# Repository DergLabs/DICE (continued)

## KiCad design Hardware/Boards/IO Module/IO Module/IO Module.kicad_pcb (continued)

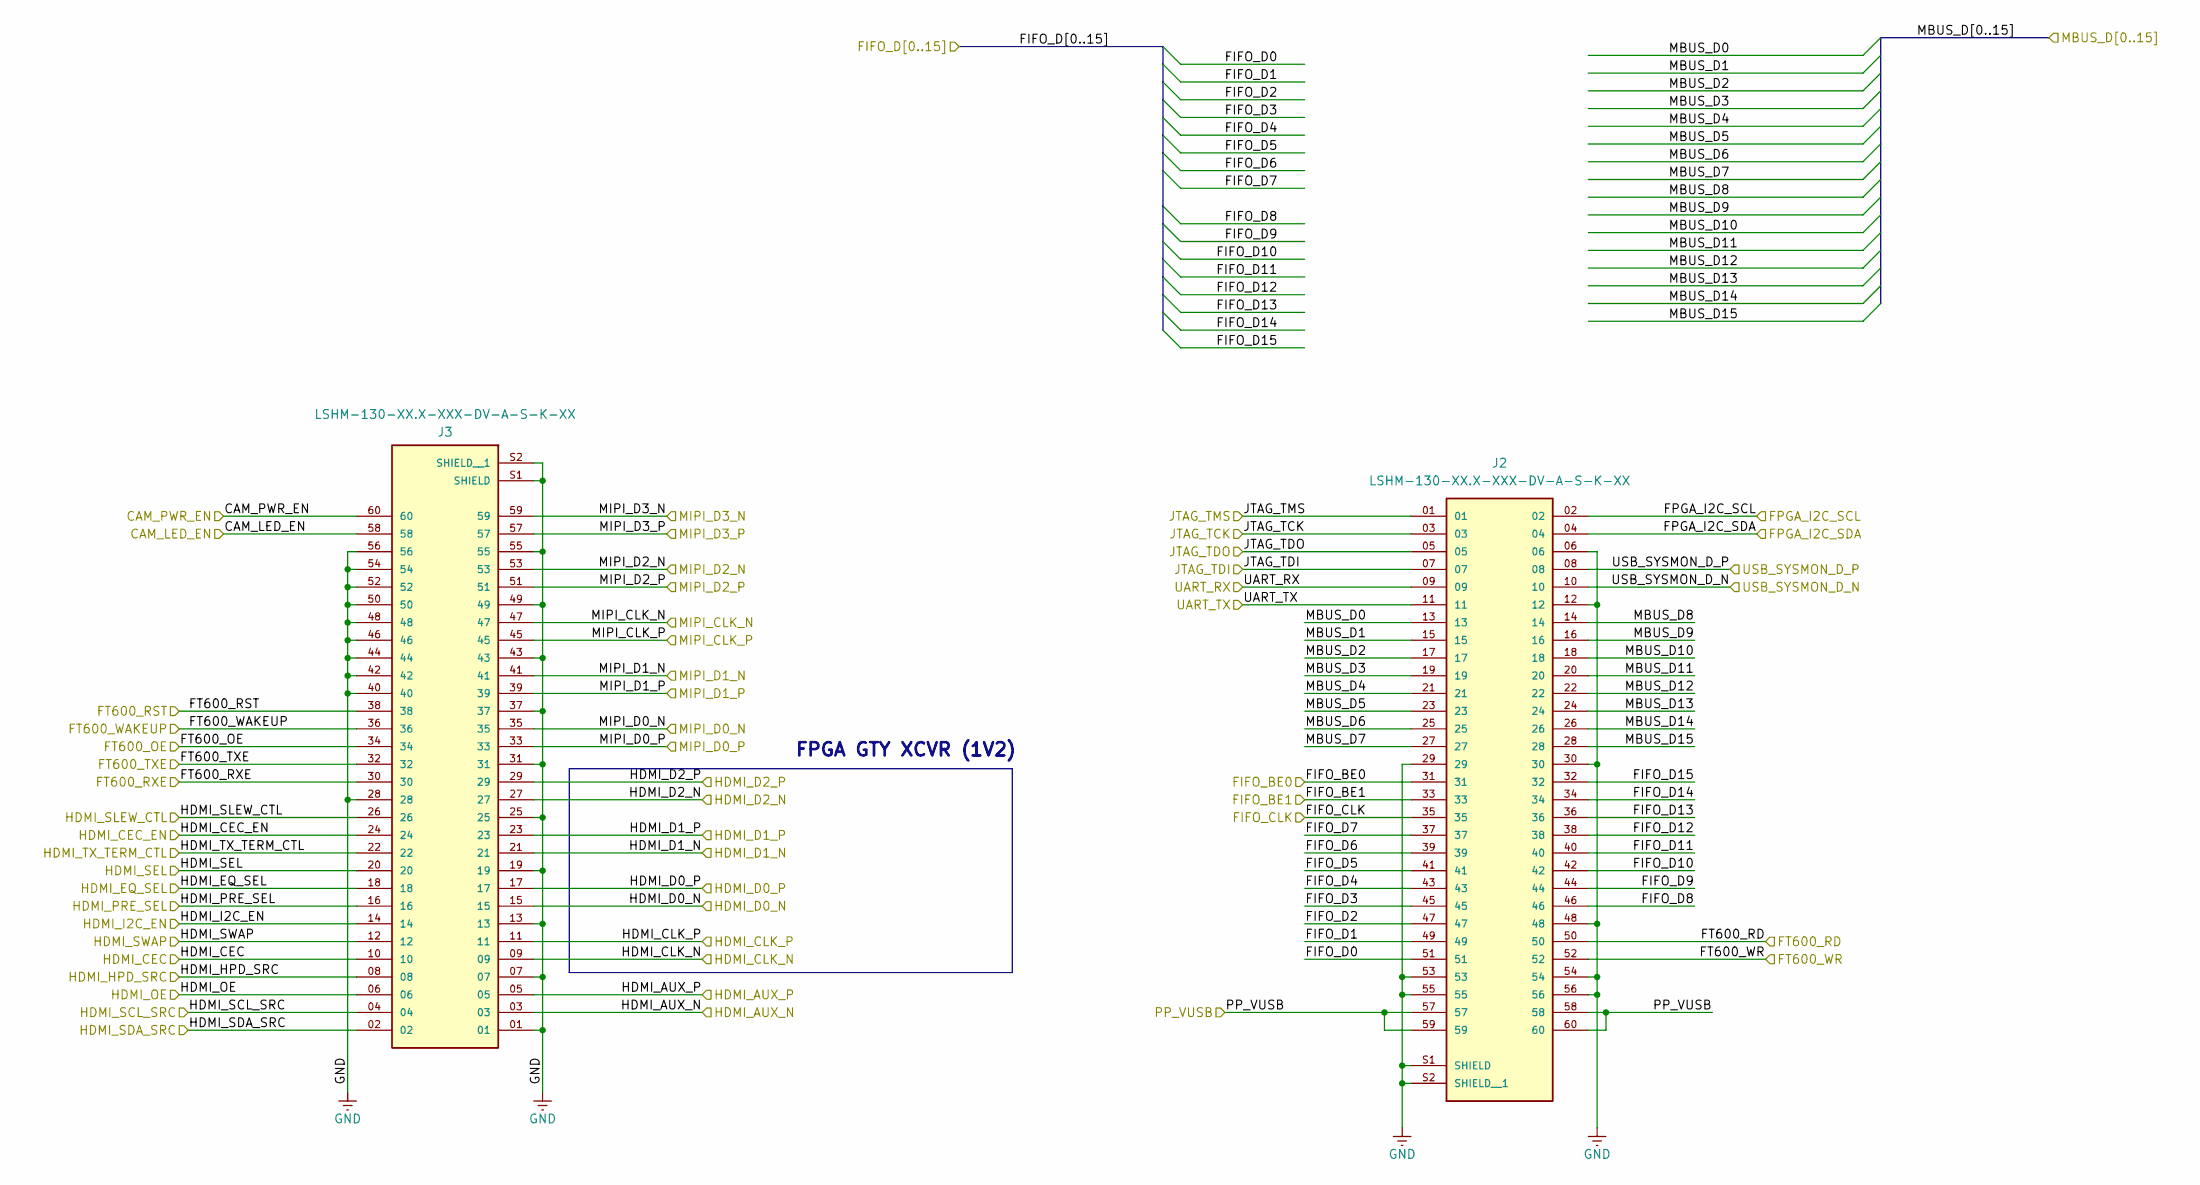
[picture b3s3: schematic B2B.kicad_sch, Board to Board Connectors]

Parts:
J2, J3: LSHM-130-XX.X-XXX-DV-A-S-K-XX; SAMTEC_LSHM-130-XX.X-XXX-DV-A-S-K-XX; PARTREV G

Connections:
/Top/B2B/CAM_LED_EN: J3.58; also elsewhere on the board
/Top/B2B/CAM_PWR_EN: J3.60; also elsewhere on the board
/Top/B2B/FIFO_BE0: J2.31; also elsewhere on the board
/Top/B2B/FIFO_BE1: J2.33; also elsewhere on the board
/Top/B2B/FIFO_CLK: J2.35; also elsewhere on the board
/Top/B2B/FIFO_D0: J2.51; also elsewhere on the board
/Top/B2B/FIFO_D1: J2.49; also elsewhere on the board
/Top/B2B/FIFO_D2: J2.47; also elsewhere on the board
/Top/B2B/FIFO_D3: J2.45; also elsewhere on the board
/Top/B2B/FIFO_D4: J2.43; also elsewhere on the board
/Top/B2B/FIFO_D5: J2.41; also elsewhere on the board
/Top/B2B/FIFO_D6: J2.39; also elsewhere on the board
/Top/B2B/FIFO_D7: J2.37; also elsewhere on the board
/Top/B2B/FIFO_D8: J2.46; also elsewhere on the board
/Top/B2B/FIFO_D9: J2.44; also elsewhere on the board
/Top/B2B/FIFO_D10: J2.42; also elsewhere on the board
/Top/B2B/FIFO_D11: J2.40; also elsewhere on the board
/Top/B2B/FIFO_D12: J2.38; also elsewhere on the board
/Top/B2B/FIFO_D13: J2.36; also elsewhere on the board
/Top/B2B/FIFO_D14: J2.34; also elsewhere on the board
/Top/B2B/FIFO_D15: J2.32; also elsewhere on the board
/Top/B2B/FPGA_I2C_SCL: J2.02; also elsewhere on the board
/Top/B2B/FPGA_I2C_SDA: J2.04; also elsewhere on the board
/Top/B2B/FT600_OE: J3.34; also elsewhere on the board
/Top/B2B/FT600_RD: J2.50; also elsewhere on the board
/Top/B2B/FT600_RST: J3.38; also elsewhere on the board
/Top/B2B/FT600_RXE: J3.30; also elsewhere on the board
/Top/B2B/FT600_TXE: J3.32; also elsewhere on the board
/Top/B2B/FT600_WAKEUP: J3.36; also elsewhere on the board
/Top/B2B/FT600_WR: J2.52; also elsewhere on the board
/Top/B2B/HDMI_AUX_N: J3.03; also elsewhere on the board
/Top/B2B/HDMI_AUX_P: J3.05; also elsewhere on the board
/Top/B2B/HDMI_CEC: J3.10; also elsewhere on the board
/Top/B2B/HDMI_CEC_EN: J3.24; also elsewhere on the board
/Top/B2B/HDMI_CLK_N: J3.09; also elsewhere on the board
/Top/B2B/HDMI_CLK_P: J3.11; also elsewhere on the board
/Top/B2B/HDMI_D0_N: J3.15; also elsewhere on the board
/Top/B2B/HDMI_D0_P: J3.17; also elsewhere on the board
/Top/B2B/HDMI_D1_N: J3.21; also elsewhere on the board
/Top/B2B/HDMI_D1_P: J3.23; also elsewhere on the board
/Top/B2B/HDMI_D2_N: J3.27; also elsewhere on the board
/Top/B2B/HDMI_D2_P: J3.29; also elsewhere on the board
/Top/B2B/HDMI_EQ_SEL: J3.18; also elsewhere on the board
/Top/B2B/HDMI_HPD_SRC: J3.08; also elsewhere on the board
/Top/B2B/HDMI_I2C_EN: J3.14; also elsewhere on the board
/Top/B2B/HDMI_OE: J3.06; also elsewhere on the board
/Top/B2B/HDMI_PRE_SEL: J3.16; also elsewhere on the board
/Top/B2B/HDMI_SCL_SRC: J3.04; also elsewhere on the board
/Top/B2B/HDMI_SDA_SRC: J3.02; also elsewhere on the board
/Top/B2B/HDMI_SEL: J3.20; also elsewhere on the board
/Top/B2B/HDMI_SLEW_CTL: J3.26; also elsewhere on the board
/Top/B2B/HDMI_SWAP: J3.12; also elsewhere on the board
/Top/B2B/HDMI_TX_TERM_CTL: J3.22; also elsewhere on the board
/Top/B2B/JTAG_TCK: J2.03; also elsewhere on the board
/Top/B2B/JTAG_TDI: J2.07; also elsewhere on the board
/Top/B2B/JTAG_TDO: J2.05; also elsewhere on the board
/Top/B2B/JTAG_TMS: J2.01; also elsewhere on the board
/Top/B2B/MBUS_D0: J2.13; also elsewhere on the board
/Top/B2B/MBUS_D1: J2.15; also elsewhere on the board
/Top/B2B/MBUS_D2: J2.17; also elsewhere on the board
/Top/B2B/MBUS_D3: J2.19; also elsewhere on the board
/Top/B2B/MBUS_D4: J2.21; also elsewhere on the board
/Top/B2B/MBUS_D5: J2.23; also elsewhere on the board
/Top/B2B/MBUS_D6: J2.25; also elsewhere on the board
/Top/B2B/MBUS_D7: J2.27; also elsewhere on the board
/Top/B2B/MBUS_D8: J2.14; also elsewhere on the board
/Top/B2B/MBUS_D9: J2.16; also elsewhere on the board
/Top/B2B/MBUS_D10: J2.18; also elsewhere on the board
/Top/B2B/MBUS_D11: J2.20; also elsewhere on the board
/Top/B2B/MBUS_D12: J2.22; also elsewhere on the board
/Top/B2B/MBUS_D13: J2.24; also elsewhere on the board
/Top/B2B/MBUS_D14: J2.26; also elsewhere on the board
/Top/B2B/MBUS_D15: J2.28; also elsewhere on the board
/Top/B2B/MIPI_CLK_N: J3.47; also elsewhere on the board
/Top/B2B/MIPI_CLK_P: J3.45; also elsewhere on the board
/Top/B2B/MIPI_D0_N: J3.35; also elsewhere on the board
/Top/B2B/MIPI_D0_P: J3.33; also elsewhere on the board
/Top/B2B/MIPI_D1_N: J3.41; also elsewhere on the board
/Top/B2B/MIPI_D1_P: J3.39; also elsewhere on the board
/Top/B2B/MIPI_D2_N: J3.53; also elsewhere on the board
/Top/B2B/MIPI_D2_P: J3.51; also elsewhere on the board
/Top/B2B/MIPI_D3_N: J3.59; also elsewhere on the board
/Top/B2B/MIPI_D3_P: J3.57; also elsewhere on the board
/Top/B2B/UART_RX: J2.09; also elsewhere on the board
/Top/B2B/UART_TX: J2.11; also elsewhere on the board
/Top/B2B/USB_SYSMON_D_N: J2.10; also elsewhere on the board
/Top/B2B/USB_SYSMON_D_P: J2.08; also elsewhere on the board
/Top/PP_VUSB: J2.57, J2.58, J2.59, J2.60; also elsewhere on the board
GND: J2.06, J2.12, J2.29, J2.30, J2.48, J2.53, J2.54, J2.55, J2.56, J2.S1 (SHIELD), J2.S2 (SHIELD__1), J3.01, J3.07, J3.13, J3.19, J3.25, J3.28, J3.31, J3.37, J3.40, J3.42, J3.43, J3.44, J3.46, J3.48, J3.49, J3.50, J3.52, J3.54, J3.55, J3.56, J3.S1 (SHIELD), J3.S2 (SHIELD__1); also elsewhere on the board

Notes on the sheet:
FPGA GTY XCVR (1V2)

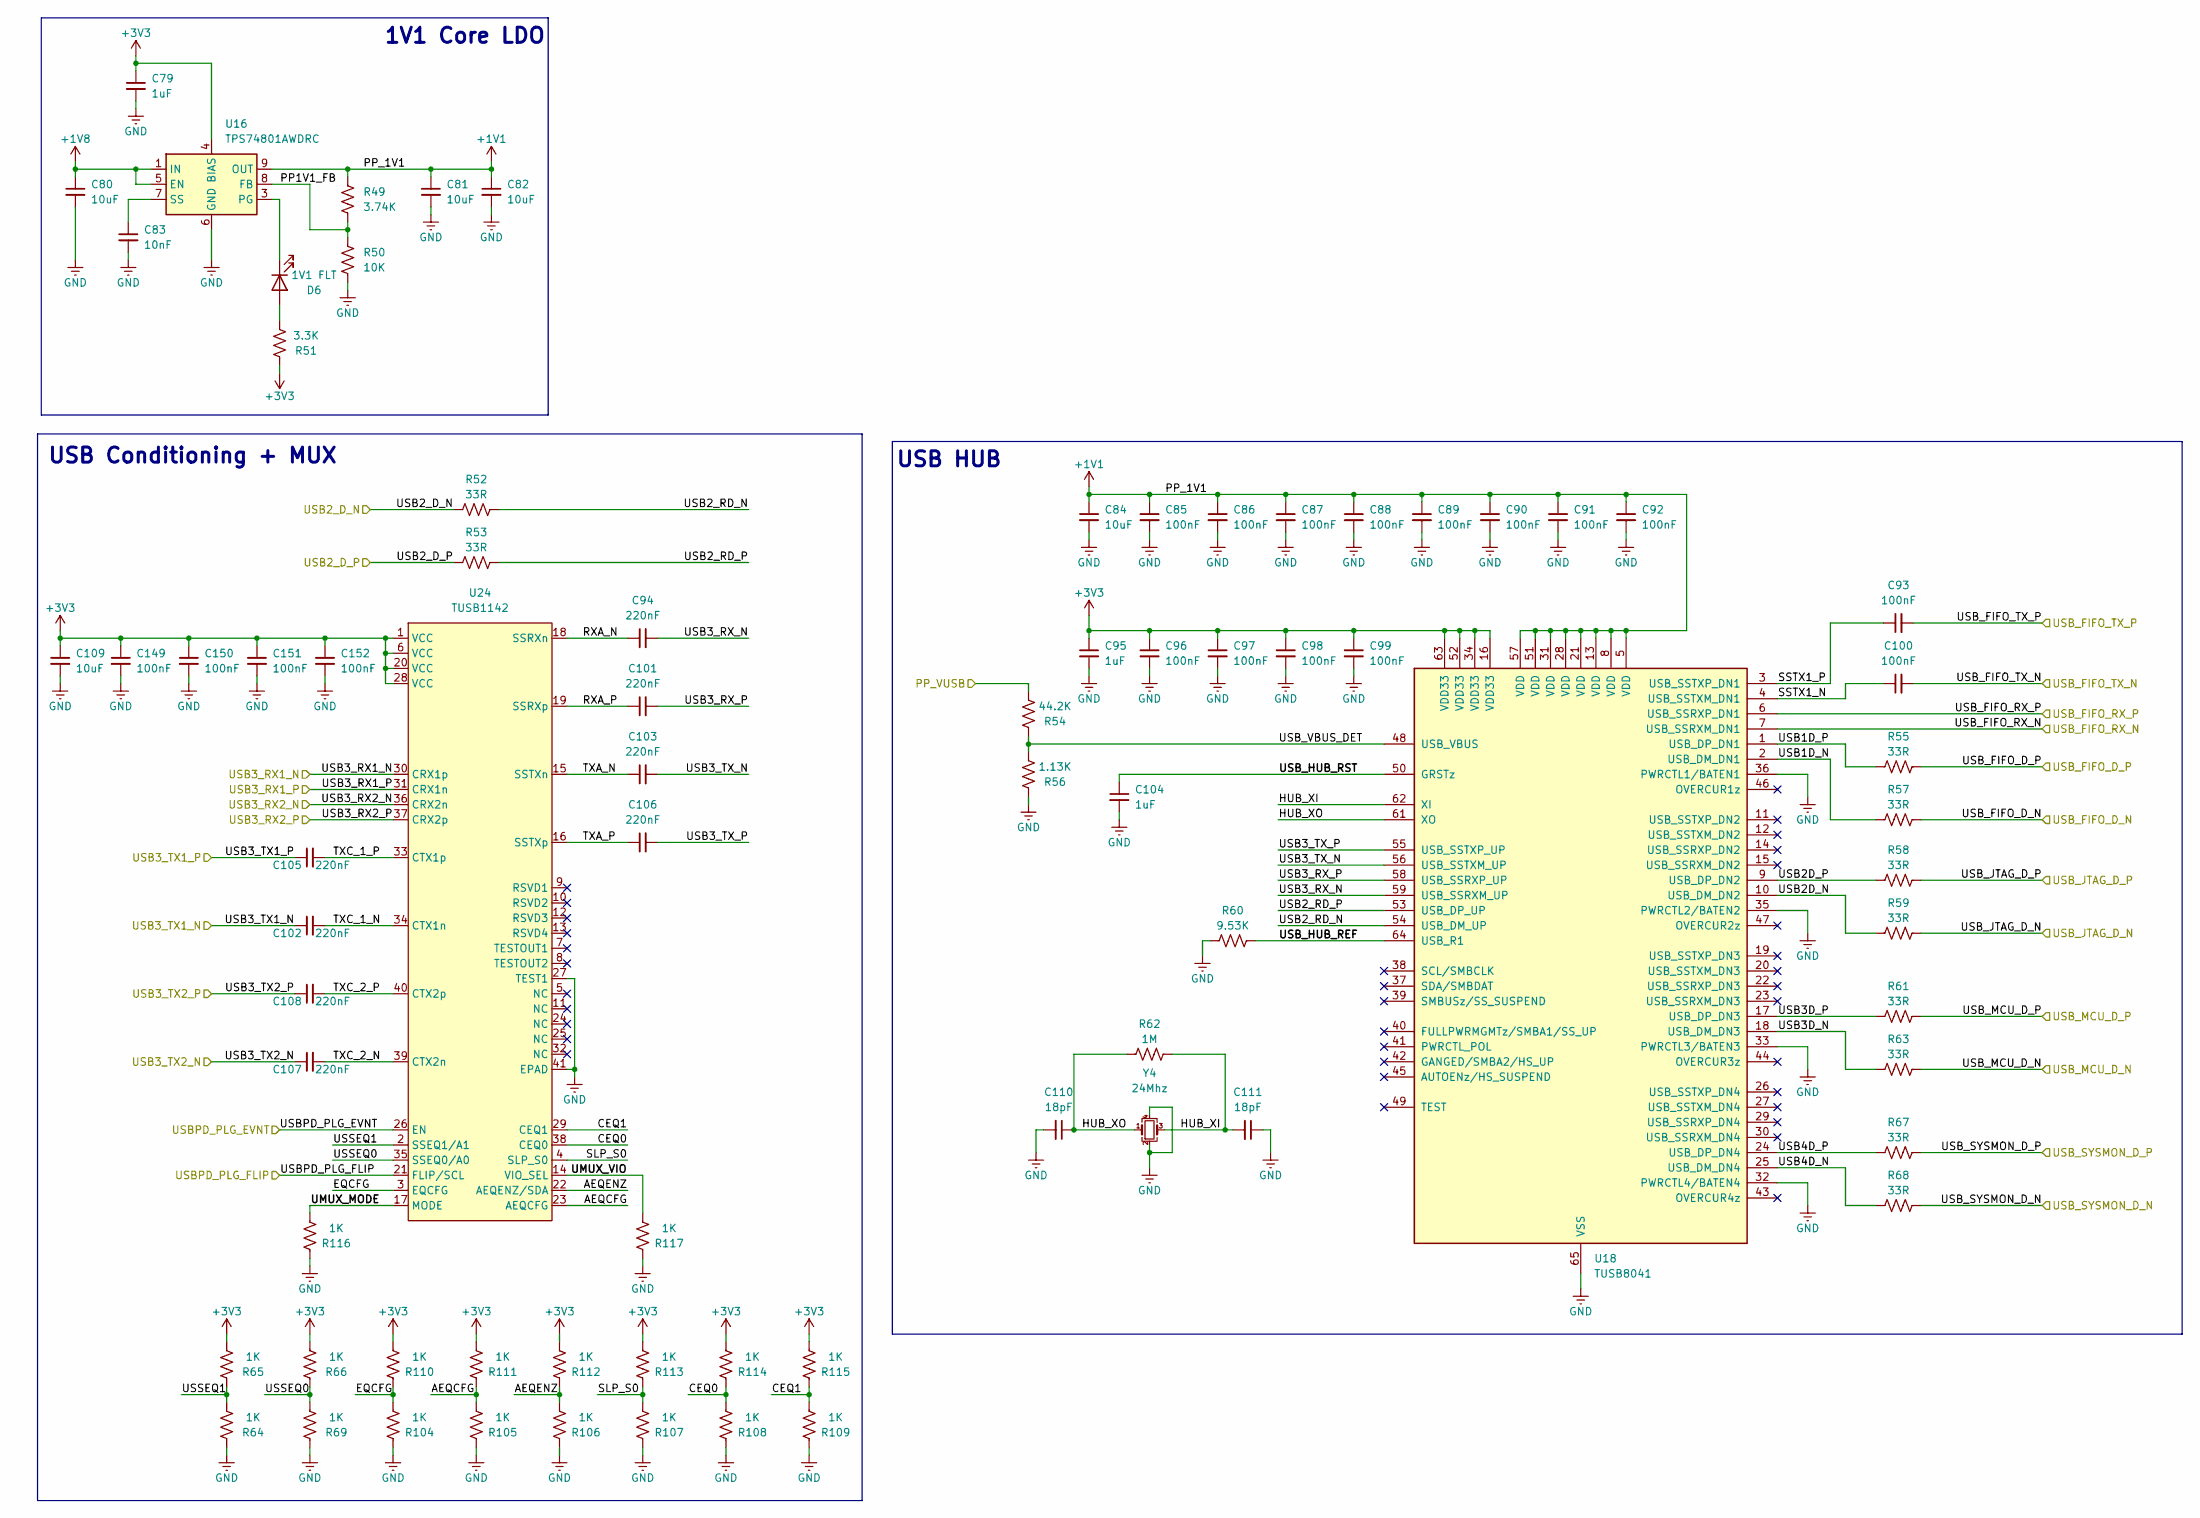
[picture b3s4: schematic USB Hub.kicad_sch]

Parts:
C79, C95, C104: 1uF; C_0201_0603Metric
C80, C81, C82, C84, C109: 10uF; C_0603_1608Metric
C83: 10nF; C_0201_0603Metric
C85, C86, C87, C88, C89, C90, C91, C92, C93, C96, C97, C98, C99, C100, C149, C150, C151, C152: 100nF; C_0201_0603Metric
C94, C101, C102, C103, C105, C106, C107, C108: 220nF; C_0201_0603Metric
C110, C111: 18pF; C_0201_0603Metric
D6: 1V1 FLT; LED_0603_1608Metric
R49: 3.74K; R_0201_0603Metric
R50: 10K; R_0201_0603Metric
R51: 3.3K; R_0201_0603Metric
R52, R53, R55, R57, R58, R59, R61, R63, R67, R68: 33R; R_0201_0603Metric
R54: 44.2K; R_0201_0603Metric
R56: 1.13K; R_0201_0603Metric
R60: 9.53K; R_0201_0603Metric
R62: 1M; R_0201_0603Metric
R64, R65, R66, R69, R104, R105, R106, R107, R108, R109, R110, R111, R112, R113, R114, R115, R116, R117: 1K; R_0201_0603Metric
U16: TPS74801AWDRC; VSON-10-1EP_3x3mm_P0.5mm_EP1.65x2.4mm_ThermalVias
U18: TUSB8041; QFN-64-1EP_9x9mm_P0.5mm_EP6x6mm_ThermalVias
U24: TUSB1142; WQFN_142RNQT_TEX
Y4: 24Mhz; Oscillator_SMD_Abracon_ASE-4Pin_3.2x2.5mm

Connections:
+1V1: C81.1, C82.1, C84.1, C85.1, C86.1, C87.1, C88.1, C89.1, C90.1, C91.1, C92.1, R49.2, U16.9 (OUT), U16.10 (OUT), U18.5 (VDD), U18.8 (VDD), U18.13 (VDD), U18.21 (VDD), U18.28 (VDD), U18.31 (VDD), U18.51 (VDD), U18.57 (VDD)
+1V8: C80.1, U16.1 (IN), U16.2 (IN), U16.5 (EN); also elsewhere on the board
+3V3: C79.1, C95.1, C96.1, C97.1, C98.1, C99.1, C109.1, C149.1, C150.1, C151.1, C152.1, R51.1, R65.2, R66.2, R110.2, R111.2, R112.2, R113.2, R114.2, R115.2, U16.4 (BIAS), U18.16 (VDD33), U18.34 (VDD33), U18.52 (VDD33), U18.63 (VDD33), U24.1 (VCC), U24.6 (VCC), U24.20 (VCC), U24.28 (VCC); also elsewhere on the board
/Top/B2B/USB_SYSMON_D_N: R68.1; also elsewhere on the board
/Top/B2B/USB_SYSMON_D_P: R67.1; also elsewhere on the board
/Top/MCU/USBPD_PLG_EVNT: U24.26 (EN); also elsewhere on the board
/Top/MCU/USBPD_PLG_FLIP: U24.21 (FLIP/SCL); also elsewhere on the board
/Top/MCU/USB_MCU_D_N: R63.1; also elsewhere on the board
/Top/MCU/USB_MCU_D_P: R61.1; also elsewhere on the board
/Top/PP_VUSB: R54.2; also elsewhere on the board
/Top/Power/USB2_D_N: R52.2; also elsewhere on the board
/Top/Power/USB2_D_P: R53.2; also elsewhere on the board
/Top/Power/USB3_RX1_N: U24.30 (CRX1p); also elsewhere on the board
/Top/Power/USB3_RX1_P: U24.31 (CRX1n); also elsewhere on the board
/Top/Power/USB3_RX2_N: U24.36 (CRX2n); also elsewhere on the board
/Top/Power/USB3_RX2_P: U24.37 (CRX2p); also elsewhere on the board
/Top/Power/USB3_TX1_N: C102.1; also elsewhere on the board
/Top/Power/USB3_TX1_P: C105.1; also elsewhere on the board
/Top/Power/USB3_TX2_N: C107.1; also elsewhere on the board
/Top/Power/USB3_TX2_P: C108.1; also elsewhere on the board
/Top/USB Hub/AEQCFG: R105.2, R111.1, U24.23 (AEQCFG)
/Top/USB Hub/AEQENZ: R106.2, R112.1, U24.22 (AEQENZ/SDA)
/Top/USB Hub/CEQ0: R108.2, R114.1, U24.38 (CEQ0)
/Top/USB Hub/CEQ1: R109.2, R115.1, U24.29 (CEQ1)
/Top/USB Hub/EQCFG: R104.2, R110.1, U24.3 (EQCFG)
/Top/USB Hub/HUB_XI: C111.2, R62.1, U18.62 (XI), Y4.3
/Top/USB Hub/HUB_XO: C110.1, R62.2, U18.61 (XO), Y4.1
/Top/USB Hub/PP1V1_FB: R49.1, R50.2, U16.8 (FB)
/Top/USB Hub/RXA_N: C94.1, U24.18 (SSRXn)
/Top/USB Hub/RXA_P: C101.1, U24.19 (SSRXp)
/Top/USB Hub/SLP_S0: R107.2, R113.1, U24.4 (SLP_S0)
/Top/USB Hub/SSTX1_N: C100.1, U18.4 (USB_SSTXM_DN1)
/Top/USB Hub/SSTX1_P: C93.1, U18.3 (USB_SSTXP_DN1)
/Top/USB Hub/TXA_N: C103.1, U24.15 (SSTXn)
/Top/USB Hub/TXA_P: C106.1, U24.16 (SSTXp)
/Top/USB Hub/TXC_1_N: C102.2, U24.34 (CTX1n)
/Top/USB Hub/TXC_1_P: C105.2, U24.33 (CTX1p)
/Top/USB Hub/TXC_2_N: C107.2, U24.39 (CTX2n)
/Top/USB Hub/TXC_2_P: C108.2, U24.40 (CTX2p)
/Top/USB Hub/UMUX_MODE: R116.2, U24.17 (MODE)
/Top/USB Hub/UMUX_VIO: R117.2, U24.14 (VIO_SEL)
/Top/USB Hub/USB1D_N: R57.2, U18.2 (USB_DM_DN1)
/Top/USB Hub/USB1D_P: R55.2, U18.1 (USB_DP_DN1)
/Top/USB Hub/USB2D_N: R59.2, U18.10 (USB_DM_DN2)
/Top/USB Hub/USB2D_P: R58.2, U18.9 (USB_DP_DN2)
/Top/USB Hub/USB2_RD_N: R52.1, U18.54 (USB_DM_UP)
/Top/USB Hub/USB2_RD_P: R53.1, U18.53 (USB_DP_UP)
/Top/USB Hub/USB3D_N: R63.2, U18.18 (USB_DM_DN3)
/Top/USB Hub/USB3D_P: R61.2, U18.17 (USB_DP_DN3)
/Top/USB Hub/USB3_RX_N: C94.2, U18.59 (USB_SSRXM_UP)
/Top/USB Hub/USB3_RX_P: C101.2, U18.58 (USB_SSRXP_UP)
/Top/USB Hub/USB3_TX_N: C103.2, U18.56 (USB_SSTXM_UP)
/Top/USB Hub/USB3_TX_P: C106.2, U18.55 (USB_SSTXP_UP)
/Top/USB Hub/USB4D_N: R68.2, U18.25 (USB_DM_DN4)
/Top/USB Hub/USB4D_P: R67.2, U18.24 (USB_DP_DN4)
/Top/USB Hub/USB_FIFO_D_N: R57.1; also elsewhere on the board
/Top/USB Hub/USB_FIFO_D_P: R55.1; also elsewhere on the board
/Top/USB Hub/USB_FIFO_RX_N: U18.7 (USB_SSRXM_DN1); also elsewhere on the board
/Top/USB Hub/USB_FIFO_RX_P: U18.6 (USB_SSRXP_DN1); also elsewhere on the board
/Top/USB Hub/USB_FIFO_TX_N: C100.2; also elsewhere on the board
/Top/USB Hub/USB_FIFO_TX_P: C93.2; also elsewhere on the board
/Top/USB Hub/USB_HUB_REF: R60.1, U18.64 (USB_R1)
/Top/USB Hub/USB_HUB_RST: C104.1, U18.50 (GRSTz)
/Top/USB Hub/USB_JTAG_D_N: R59.1; also elsewhere on the board
/Top/USB Hub/USB_JTAG_D_P: R58.1; also elsewhere on the board
/Top/USB Hub/USB_VBUS_DET: R54.1, R56.2, U18.48 (USB_VBUS)
/Top/USB Hub/USSEQ0: R66.1, R69.2, U24.35 (SSEQ0/A0)
/Top/USB Hub/USSEQ1: R64.2, R65.1, U24.2 (SSEQ1/A1)
GND: C79.2, C80.2, C81.2, C82.2, C83.2, C84.2, C85.2, C86.2, C87.2, C88.2, C89.2, C90.2, C91.2, C92.2, C95.2, C96.2, C97.2, C98.2, C99.2, C104.2, C109.2, C110.2, C111.1, C149.2, C150.2, C151.2, C152.2, R50.1, R56.1, R60.2, R64.1, R69.1, R104.1, R105.1, R106.1, R107.1, R108.1, R109.1, R116.1, R117.1, U16.6 (GND), U16.11 (GND), U18.32 (PWRCTL4/BATEN4), U18.33 (PWRCTL3/BATEN3), U18.35 (PWRCTL2/BATEN2), U18.36 (PWRCTL1/BATEN1), U18.65 (VSS), U24.27 (TEST1), U24.41 (EPAD), Y4.2, Y4.4; also elsewhere on the board
unnamed: D6.2 (A), R51.2
unnamed: D6.1 (K), U16.3 (PG)
unnamed: C83.1, U16.7 (SS)

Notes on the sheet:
USB Conditioning + MUX
1V1 Core LDO
USB HUB

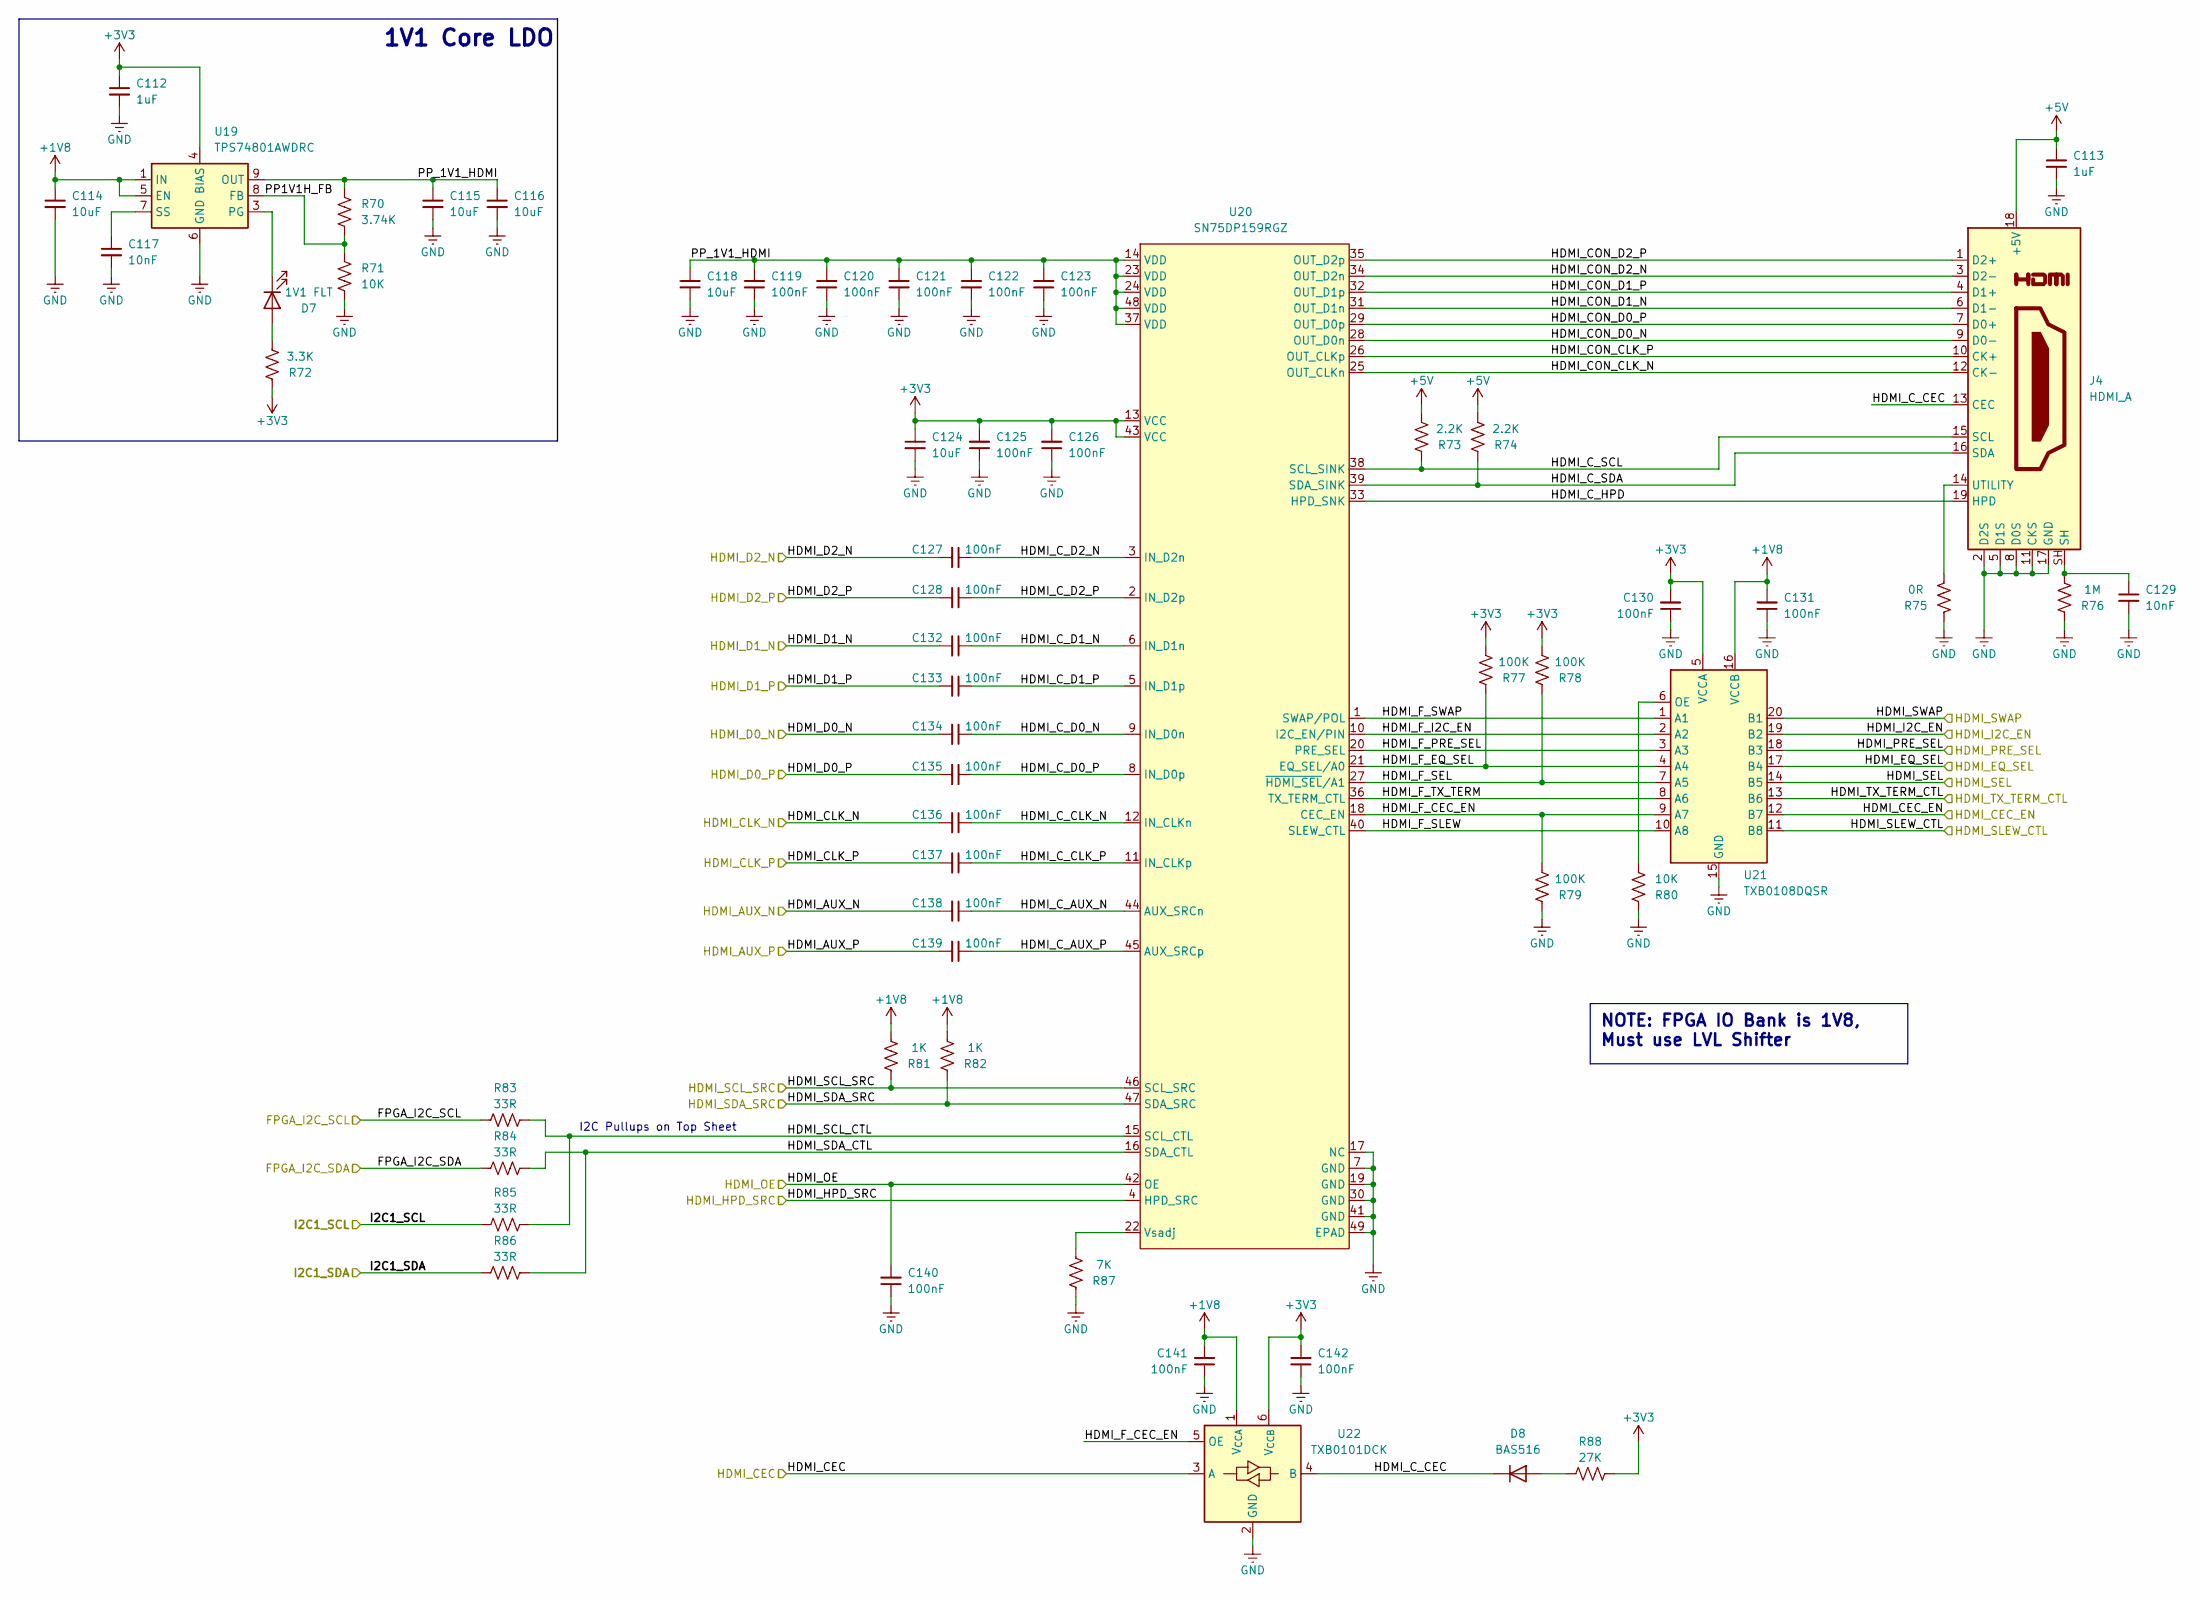
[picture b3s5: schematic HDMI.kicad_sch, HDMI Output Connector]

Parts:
C112, C113: 1uF; C_0201_0603Metric
C114, C115, C116, C118, C124: 10uF; C_0603_1608Metric
C117, C129: 10nF; C_0201_0603Metric
C119, C120, C121, C122, C123, C125, C126, C127, C128, C130, C131, C132, C133, C134, C135, C136, C137, C138, C139, C140, C141, C142: 100nF; C_0201_0603Metric
D7: 1V1 FLT; LED_0603_1608Metric
D8: BAS516; D_SOD-523
J4: HDMI_A; HDMI_A_Molex_208658-1001_Horizontal
R70: 3.74K; R_0201_0603Metric
R71, R80: 10K; R_0201_0603Metric
R72: 3.3K; R_0201_0603Metric
R73, R74: 2.2K; R_0201_0603Metric
R75: 0R; R_0201_0603Metric
R76: 1M; R_0201_0603Metric
R77, R78, R79: 100K; R_0201_0603Metric
R81, R82: 1K; R_0201_0603Metric
R83, R84, R85, R86: 33R; R_0201_0603Metric
R87: 7K; R_0201_0603Metric
R88: 27K; R_0201_0603Metric
U19: TPS74801AWDRC; VSON-10-1EP_3x3mm_P0.5mm_EP1.65x2.4mm_ThermalVias
U20: SN75DP159RGZ; QFN-48-1EP_7x7mm_P0.5mm_EP5.1x5.1mm
U21: TXB0108DQSR; USON-20_2x4mm_P0.4mm
U22: TXB0101DCK; SOT-363_SC-70-6

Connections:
+1V8: C114.1, C131.2, C141.2, R81.2, R82.2, U19.1 (IN), U19.2 (IN), U19.5 (EN), U21.16 (VCCB), U22.1 (V_{CCA}); also elsewhere on the board
+3V3: C112.1, C124.1, C125.2, C126.2, C130.2, C142.2, R72.1, R77.2, R78.2, R88.1, U19.4 (BIAS), U20.13 (VCC), U20.43 (VCC), U21.5 (VCCA), U22.6 (V_{CCB}); also elsewhere on the board
+5V: C113.1, J4.18 (+5V), R73.2, R74.2
/Top/B2B/FPGA_I2C_SCL: R83.2; also elsewhere on the board
/Top/B2B/FPGA_I2C_SDA: R84.2; also elsewhere on the board
/Top/B2B/HDMI_AUX_N: C138.2; also elsewhere on the board
/Top/B2B/HDMI_AUX_P: C139.2; also elsewhere on the board
/Top/B2B/HDMI_CEC: U22.3 (A); also elsewhere on the board
/Top/B2B/HDMI_CEC_EN: U21.12 (B7); also elsewhere on the board
/Top/B2B/HDMI_CLK_N: C136.2; also elsewhere on the board
/Top/B2B/HDMI_CLK_P: C137.2; also elsewhere on the board
/Top/B2B/HDMI_D0_N: C134.2; also elsewhere on the board
/Top/B2B/HDMI_D0_P: C135.2; also elsewhere on the board
/Top/B2B/HDMI_D1_N: C132.2; also elsewhere on the board
/Top/B2B/HDMI_D1_P: C133.2; also elsewhere on the board
/Top/B2B/HDMI_D2_N: C127.2; also elsewhere on the board
/Top/B2B/HDMI_D2_P: C128.2; also elsewhere on the board
/Top/B2B/HDMI_EQ_SEL: U21.17 (B4); also elsewhere on the board
/Top/B2B/HDMI_HPD_SRC: U20.4 (HPD_SRC); also elsewhere on the board
/Top/B2B/HDMI_I2C_EN: U21.19 (B2); also elsewhere on the board
/Top/B2B/HDMI_OE: C140.2, U20.42 (OE); also elsewhere on the board
/Top/B2B/HDMI_PRE_SEL: U21.18 (B3); also elsewhere on the board
/Top/B2B/HDMI_SCL_SRC: R81.1, U20.46 (SCL_SRC); also elsewhere on the board
/Top/B2B/HDMI_SDA_SRC: R82.1, U20.47 (SDA_SRC); also elsewhere on the board
/Top/B2B/HDMI_SEL: U21.14 (B5); also elsewhere on the board
/Top/B2B/HDMI_SLEW_CTL: U21.11 (B8); also elsewhere on the board
/Top/B2B/HDMI_SWAP: U21.20 (B1); also elsewhere on the board
/Top/B2B/HDMI_TX_TERM_CTL: U21.13 (B6); also elsewhere on the board
/Top/Camera FPC/I2C1_SCL: R85.2; also elsewhere on the board
/Top/Camera FPC/I2C1_SDA: R86.2; also elsewhere on the board
/Top/HDMI/HDMI_CON_CLK_N: J4.12 (CK-), U20.25 (OUT_CLKn)
/Top/HDMI/HDMI_CON_CLK_P: J4.10 (CK+), U20.26 (OUT_CLKp)
/Top/HDMI/HDMI_CON_D0_N: J4.9 (D0-), U20.28 (OUT_D0n)
/Top/HDMI/HDMI_CON_D0_P: J4.7 (D0+), U20.29 (OUT_D0p)
/Top/HDMI/HDMI_CON_D1_N: J4.6 (D1-), U20.31 (OUT_D1n)
/Top/HDMI/HDMI_CON_D1_P: J4.4 (D1+), U20.32 (OUT_D1p)
/Top/HDMI/HDMI_CON_D2_N: J4.3 (D2-), U20.34 (OUT_D2n)
/Top/HDMI/HDMI_CON_D2_P: J4.1 (D2+), U20.35 (OUT_D2p)
/Top/HDMI/HDMI_C_AUX_N: C138.1, U20.44 (AUX_SRCn)
/Top/HDMI/HDMI_C_AUX_P: C139.1, U20.45 (AUX_SRCp)
/Top/HDMI/HDMI_C_CEC: D8.1 (K), J4.13 (CEC), U22.4 (B)
/Top/HDMI/HDMI_C_CLK_N: C136.1, U20.12 (IN_CLKn)
/Top/HDMI/HDMI_C_CLK_P: C137.1, U20.11 (IN_CLKp)
/Top/HDMI/HDMI_C_D0_N: C134.1, U20.9 (IN_D0n)
/Top/HDMI/HDMI_C_D0_P: C135.1, U20.8 (IN_D0p)
/Top/HDMI/HDMI_C_D1_N: C132.1, U20.6 (IN_D1n)
/Top/HDMI/HDMI_C_D1_P: C133.1, U20.5 (IN_D1p)
/Top/HDMI/HDMI_C_D2_N: C127.1, U20.3 (IN_D2n)
/Top/HDMI/HDMI_C_D2_P: C128.1, U20.2 (IN_D2p)
/Top/HDMI/HDMI_C_HPD: J4.19 (HPD), U20.33 (HPD_SNK)
/Top/HDMI/HDMI_C_SCL: J4.15 (SCL), R73.1, U20.38 (SCL_SINK)
/Top/HDMI/HDMI_C_SDA: J4.16 (SDA), R74.1, U20.39 (SDA_SINK)
/Top/HDMI/HDMI_F_CEC_EN: R79.2, U20.18 (CEC_EN), U21.9 (A7), U22.5 (OE)
/Top/HDMI/HDMI_F_EQ_SEL: R77.1, U20.21 (EQ_SEL/A0), U21.4 (A4)
/Top/HDMI/HDMI_F_I2C_EN: U20.10 (I2C_EN/PIN), U21.2 (A2)
/Top/HDMI/HDMI_F_PRE_SEL: U20.20 (PRE_SEL), U21.3 (A3)
/Top/HDMI/HDMI_F_SEL: R78.1, U20.27 (~HDMI_SEL/A1), U21.7 (A5)
/Top/HDMI/HDMI_F_SLEW: U20.40 (SLEW_CTL), U21.10 (A8)
/Top/HDMI/HDMI_F_SWAP: U20.1 (SWAP/POL), U21.1 (A1)
/Top/HDMI/HDMI_F_TX_TERM: U20.36 (TX_TERM_CTL), U21.8 (A6)
/Top/HDMI/HDMI_SCL_CTL: R83.1, R85.1, U20.15 (SCL_CTL)
/Top/HDMI/HDMI_SDA_CTL: R84.1, R86.1, U20.16 (SDA_CTL)
/Top/HDMI/PP1V1H_FB: R70.1, R71.2, U19.8 (FB)
/Top/HDMI/PP_1V1_HDMI: C115.1, C116.1, C118.1, C119.2, C120.2, C121.2, C122.2, C123.2, R70.2, U19.9 (OUT), U19.10 (OUT), U20.14 (VDD), U20.23 (VDD), U20.24 (VDD), U20.37 (VDD), U20.48 (VDD)
GND: C112.2, C113.2, C114.2, C115.2, C116.2, C117.2, C118.2, C119.1, C120.1, C121.1, C122.1, C123.1, C124.2, C125.1, C126.1, C129.2, C130.1, C131.1, C140.1, C141.1, C142.1, J4.2 (D2S), J4.5 (D1S), J4.8 (D0S), J4.11 (CKS), J4.17 (GND), R71.1, R75.1, R76.1, R79.1, R80.1, R87.1, U19.6 (GND), U19.11 (GND), U20.7 (GND), U20.17 (NC), U20.19 (GND), U20.30 (GND), U20.41 (GND), U20.49 (EPAD), U21.15 (GND), U22.2 (GND); also elsewhere on the board
unnamed: C129.1, J4.SH, R76.2
unnamed: D7.2 (A), R72.2
unnamed: D7.1 (K), U19.3 (PG)
unnamed: D8.2 (A), R88.2
unnamed: J4.14 (UTILITY), R75.2
unnamed: C117.1, U19.7 (SS)
unnamed: R87.2, U20.22 (Vsadj)
unnamed: R80.2, U21.6 (OE)

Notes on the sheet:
NOTE: FPGA IO Bank is 1V8, Must use LVL Shifter
1V1 Core LDO
I2C Pullups on Top Sheet

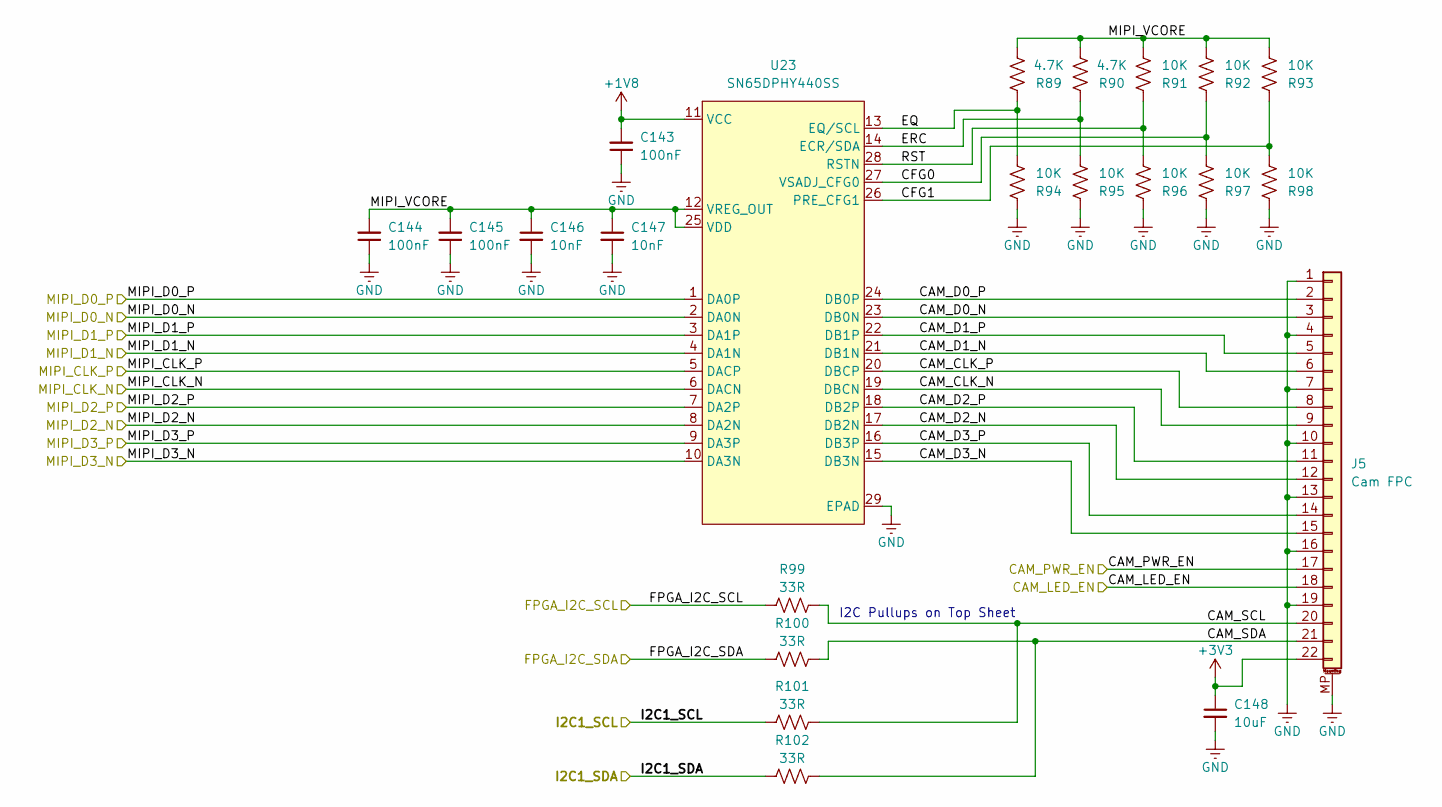
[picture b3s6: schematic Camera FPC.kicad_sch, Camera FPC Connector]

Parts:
C143, C144, C145: 100nF; C_0201_0603Metric
C146, C147: 10nF; C_0201_0603Metric
C148: 10uF; C_0603_1608Metric
J5: Cam FPC; TE_2-1734839-2_1x22-1MP_P0.5mm_Horizontal
R89, R90: 4.7K; R_0201_0603Metric
R91, R92, R93, R94, R95, R96, R97, R98: 10K; R_0201_0603Metric
R99, R100, R101, R102: 33R; R_0201_0603Metric
U23: SN65DPHY440SS; QFN-28-1EP_3x6mm_P0.5mm_EP1.7x4.75mm

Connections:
+1V8: C143.2, U23.11 (VCC); also elsewhere on the board
+3V3: C148.1, J5.22; also elsewhere on the board
/Top/B2B/CAM_LED_EN: J5.18; also elsewhere on the board
/Top/B2B/CAM_PWR_EN: J5.17; also elsewhere on the board
/Top/B2B/FPGA_I2C_SCL: R99.2; also elsewhere on the board
/Top/B2B/FPGA_I2C_SDA: R100.2; also elsewhere on the board
/Top/B2B/MIPI_CLK_N: U23.6 (DACN); also elsewhere on the board
/Top/B2B/MIPI_CLK_P: U23.5 (DACP); also elsewhere on the board
/Top/B2B/MIPI_D0_N: U23.2 (DA0N); also elsewhere on the board
/Top/B2B/MIPI_D0_P: U23.1 (DA0P); also elsewhere on the board
/Top/B2B/MIPI_D1_N: U23.4 (DA1N); also elsewhere on the board
/Top/B2B/MIPI_D1_P: U23.3 (DA1P); also elsewhere on the board
/Top/B2B/MIPI_D2_N: U23.8 (DA2N); also elsewhere on the board
/Top/B2B/MIPI_D2_P: U23.7 (DA2P); also elsewhere on the board
/Top/B2B/MIPI_D3_N: U23.10 (DA3N); also elsewhere on the board
/Top/B2B/MIPI_D3_P: U23.9 (DA3P); also elsewhere on the board
/Top/Camera FPC/CAM_CLK_N: J5.9, U23.19 (DBCN)
/Top/Camera FPC/CAM_CLK_P: J5.8, U23.20 (DBCP)
/Top/Camera FPC/CAM_D0_N: J5.3, U23.23 (DB0N)
/Top/Camera FPC/CAM_D0_P: J5.2, U23.24 (DB0P)
/Top/Camera FPC/CAM_D1_N: J5.6, U23.21 (DB1N)
/Top/Camera FPC/CAM_D1_P: J5.5, U23.22 (DB1P)
/Top/Camera FPC/CAM_D2_N: J5.12, U23.17 (DB2N)
/Top/Camera FPC/CAM_D2_P: J5.11, U23.18 (DB2P)
/Top/Camera FPC/CAM_D3_N: J5.15, U23.15 (DB3N)
/Top/Camera FPC/CAM_D3_P: J5.14, U23.16 (DB3P)
/Top/Camera FPC/CAM_SCL: J5.20, R99.1, R101.1
/Top/Camera FPC/CAM_SDA: J5.21, R100.1, R102.1
/Top/Camera FPC/CFG0: R92.1, R97.2, U23.27 (VSADJ_CFG0)
/Top/Camera FPC/CFG1: R93.1, R98.2, U23.26 (PRE_CFG1)
/Top/Camera FPC/EQ: R89.1, R94.2, U23.13 (EQ/SCL)
/Top/Camera FPC/ERC: R90.1, R95.2, U23.14 (ECR/SDA)
/Top/Camera FPC/I2C1_SCL: R101.2; also elsewhere on the board
/Top/Camera FPC/I2C1_SDA: R102.2; also elsewhere on the board
/Top/Camera FPC/MIPI_VCORE: C144.2, C145.2, C146.1, C147.1, R89.2, R90.2, R91.2, R92.2, R93.2, U23.12 (VREG_OUT), U23.25 (VDD)
/Top/Camera FPC/RST: R91.1, R96.2, U23.28 (RSTN)
GND: C143.1, C144.1, C145.1, C146.2, C147.2, C148.2, J5.1, J5.4, J5.7, J5.10, J5.13, J5.16, J5.19, J5.MP (MountPin), R94.1, R95.1, R96.1, R97.1, R98.1, U23.29 (EPAD); also elsewhere on the board

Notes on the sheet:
I2C Pullups on Top Sheet
